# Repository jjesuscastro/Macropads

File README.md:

# Macropads

This repository contains the full source files for my custom-designed mechanical macropads, featuring integrated OLED displays and programmable keys via QMK with VIAL support.

## 🛠 Project Overview

This project includes two distinct designs tailored for different productivity needs:
* **Hesu12**: A compact 12-key layout with an OLED screen.
* **Hesu14**: An expanded 14-key layout with an OLED screen.

---

## 🎹 Hardware Specifications

Both boards are designed with a focus on ease of assembly and high-performance hardware:

* **Controller Support**: Designed for Pro Micro or RP2040 Zero
* **Display**: I2C OLED modules (128x32).
* **Switches**: MX-compatible mechanical switch footprints.
* **Connectivity**: USB-C (via controller).

| Feature | Hesu12 | Hesu14 |
| :--- | :--- | :--- |
| **Key Count** | 12 Keys | 14 Keys |
| **Display** | 1x OLED | 1x OLED |
| **EDA Tool** | KiCad 8.0+ | KiCad 8.0+ |

---

## 🚀 Firmware Installation
These macropads utilize **QMK (Quantum Mechanical Keyboard)** firmware.

1. Clone the official [QMK Firmware](https://github.com/qmk/qmk_firmware) repository.
2. Copy the contents of the `/Firmware` directory into your local `qmk_firmware/keyboards/` folder.
3. Compile and flash your board using the QMK CLI:

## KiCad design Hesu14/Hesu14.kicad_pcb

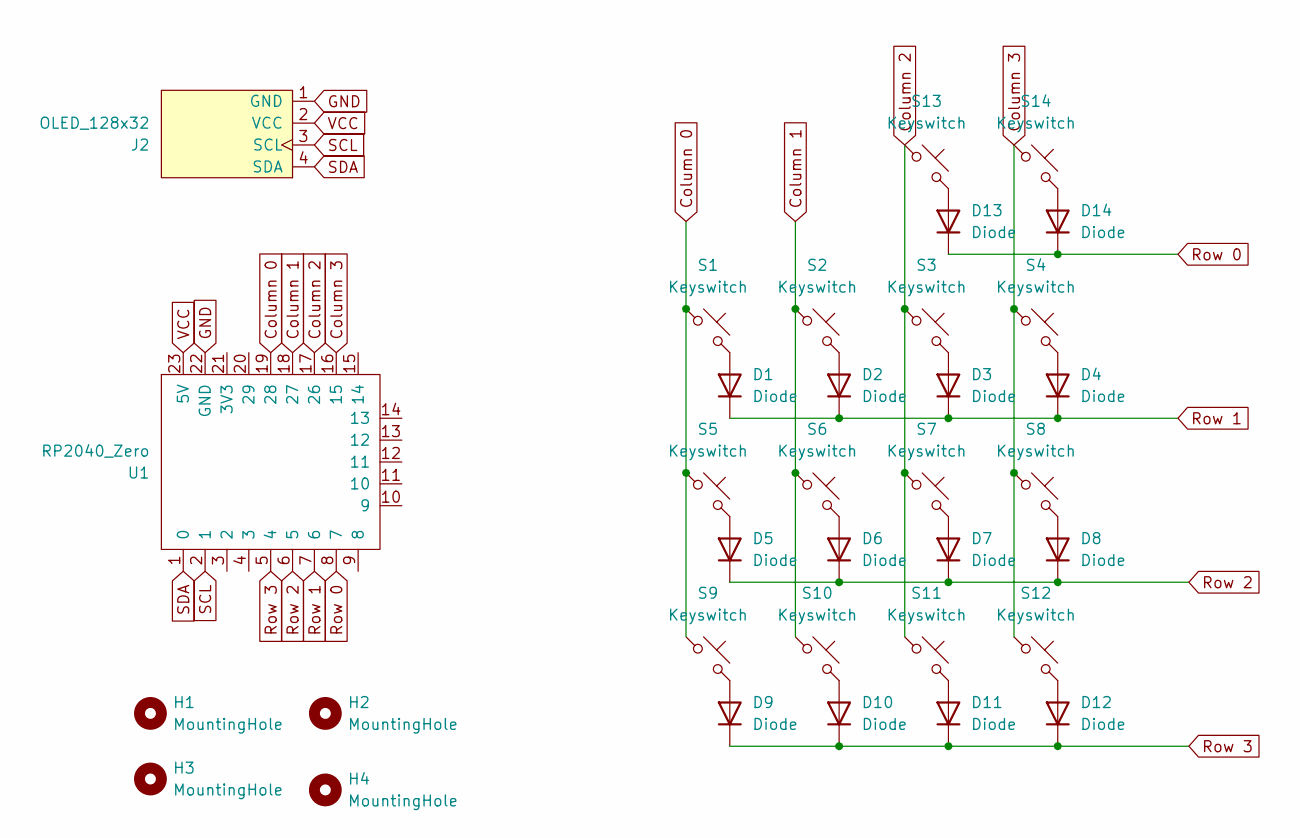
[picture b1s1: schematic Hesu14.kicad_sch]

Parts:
D1, D2, D3, D4, D5, D6, D7, D8, D9, D10, D11, D12, D13, D14: Diode; Diode_DO-35
H1, H2, H3, H4: MountingHole; MountingHole_2.5mm
J2: OLED_128x32
S1, S2, S3, S4, S5, S6, S7, S8, S9, S10, S11, S12, S13, S14: Keyswitch; Hotswap_MX_1.00u
U1: RP2040_Zero

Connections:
Column 0: S1.1, S5.1, S9.1, U1.19 (28)
Column 1: S2.1, S6.1, S10.1, U1.18 (27)
Column 2: S3.1, S7.1, S11.1, S13.1, U1.17 (26)
Column 3: S4.1, S8.1, S12.1, S14.1, U1.16 (15)
GND: J2.1 (GND), U1.22 (GND)
unnamed: D1.2 (A), S1.2
unnamed: D2.2 (A), S2.2
unnamed: D3.2 (A), S3.2
unnamed: D4.2 (A), S4.2
unnamed: D5.2 (A), S5.2
unnamed: D6.2 (A), S6.2
unnamed: D7.2 (A), S7.2
unnamed: D8.2 (A), S8.2
unnamed: D9.2 (A), S9.2
unnamed: D10.2 (A), S10.2
unnamed: D11.2 (A), S11.2
unnamed: D12.2 (A), S12.2
unnamed: D13.2 (A), S13.2
unnamed: D14.2 (A), S14.2
Row 0: D13.1 (K), D14.1 (K), U1.8 (7)
Row 1: D1.1 (K), D2.1 (K), D3.1 (K), D4.1 (K), U1.7 (6)
Row 2: D5.1 (K), D6.1 (K), D7.1 (K), D8.1 (K), U1.6 (5)
Row 3: D9.1 (K), D10.1 (K), D11.1 (K), D12.1 (K), U1.5 (4)
SCL: J2.3 (SCL), U1.2 (1)
SDA: J2.4 (SDA), U1.1 (0)
VCC: J2.2 (VCC), U1.23 (5V)

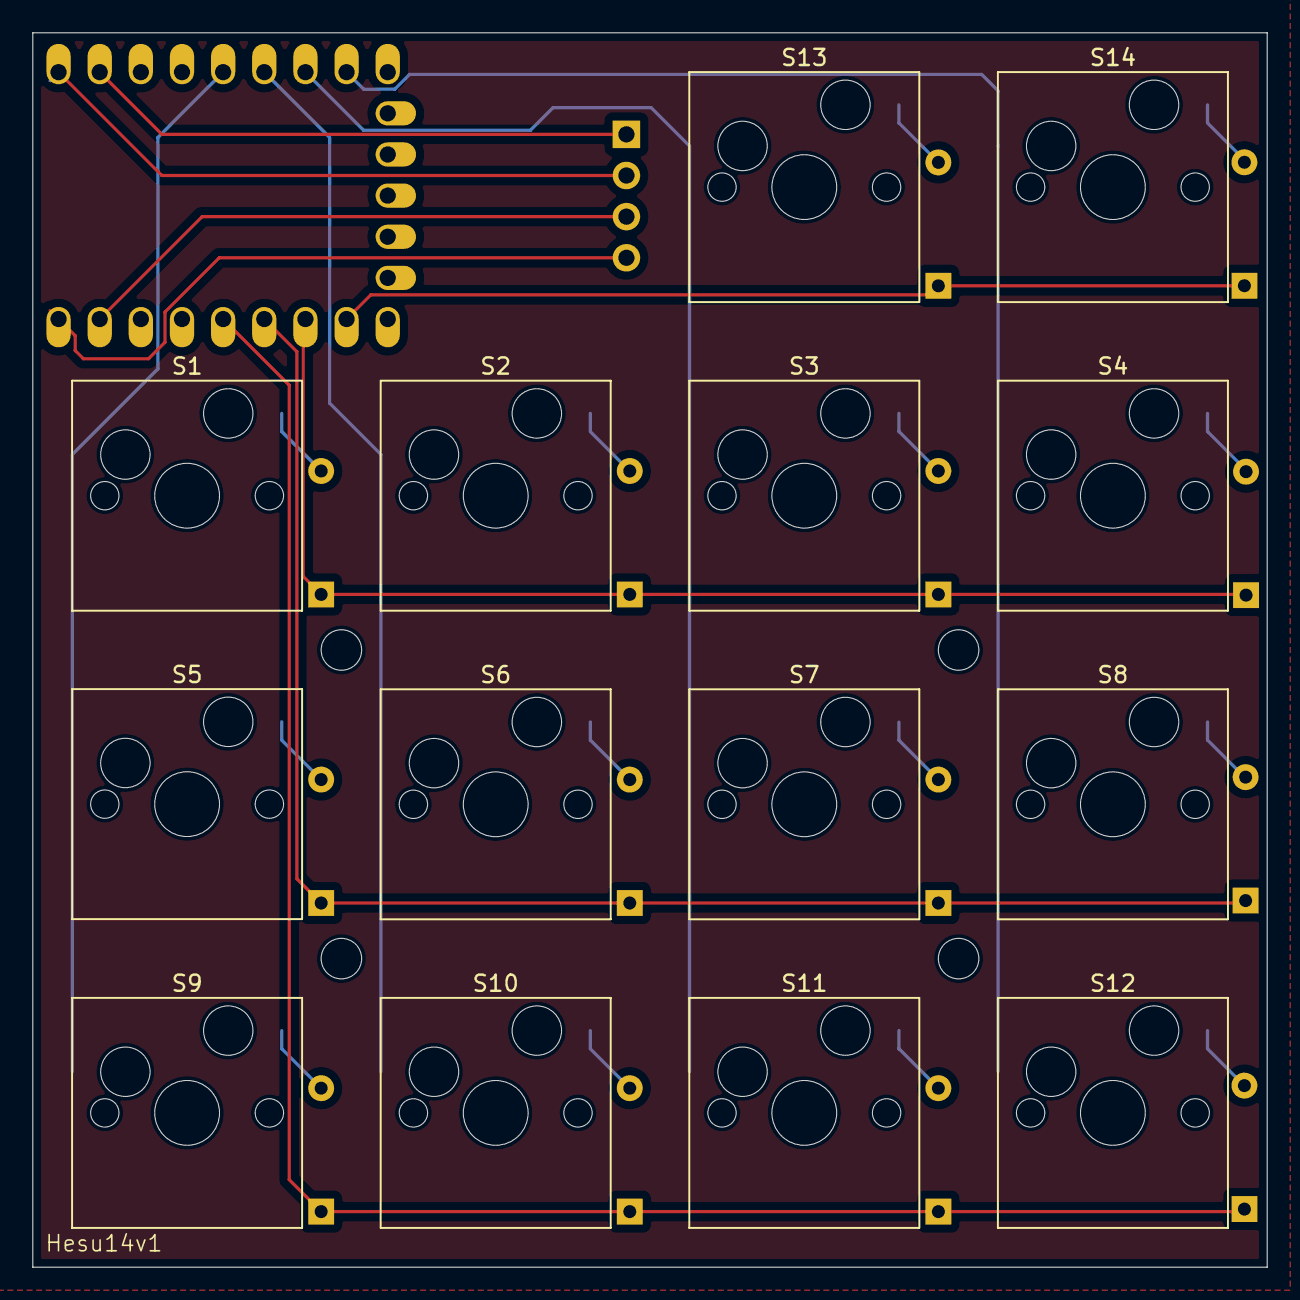
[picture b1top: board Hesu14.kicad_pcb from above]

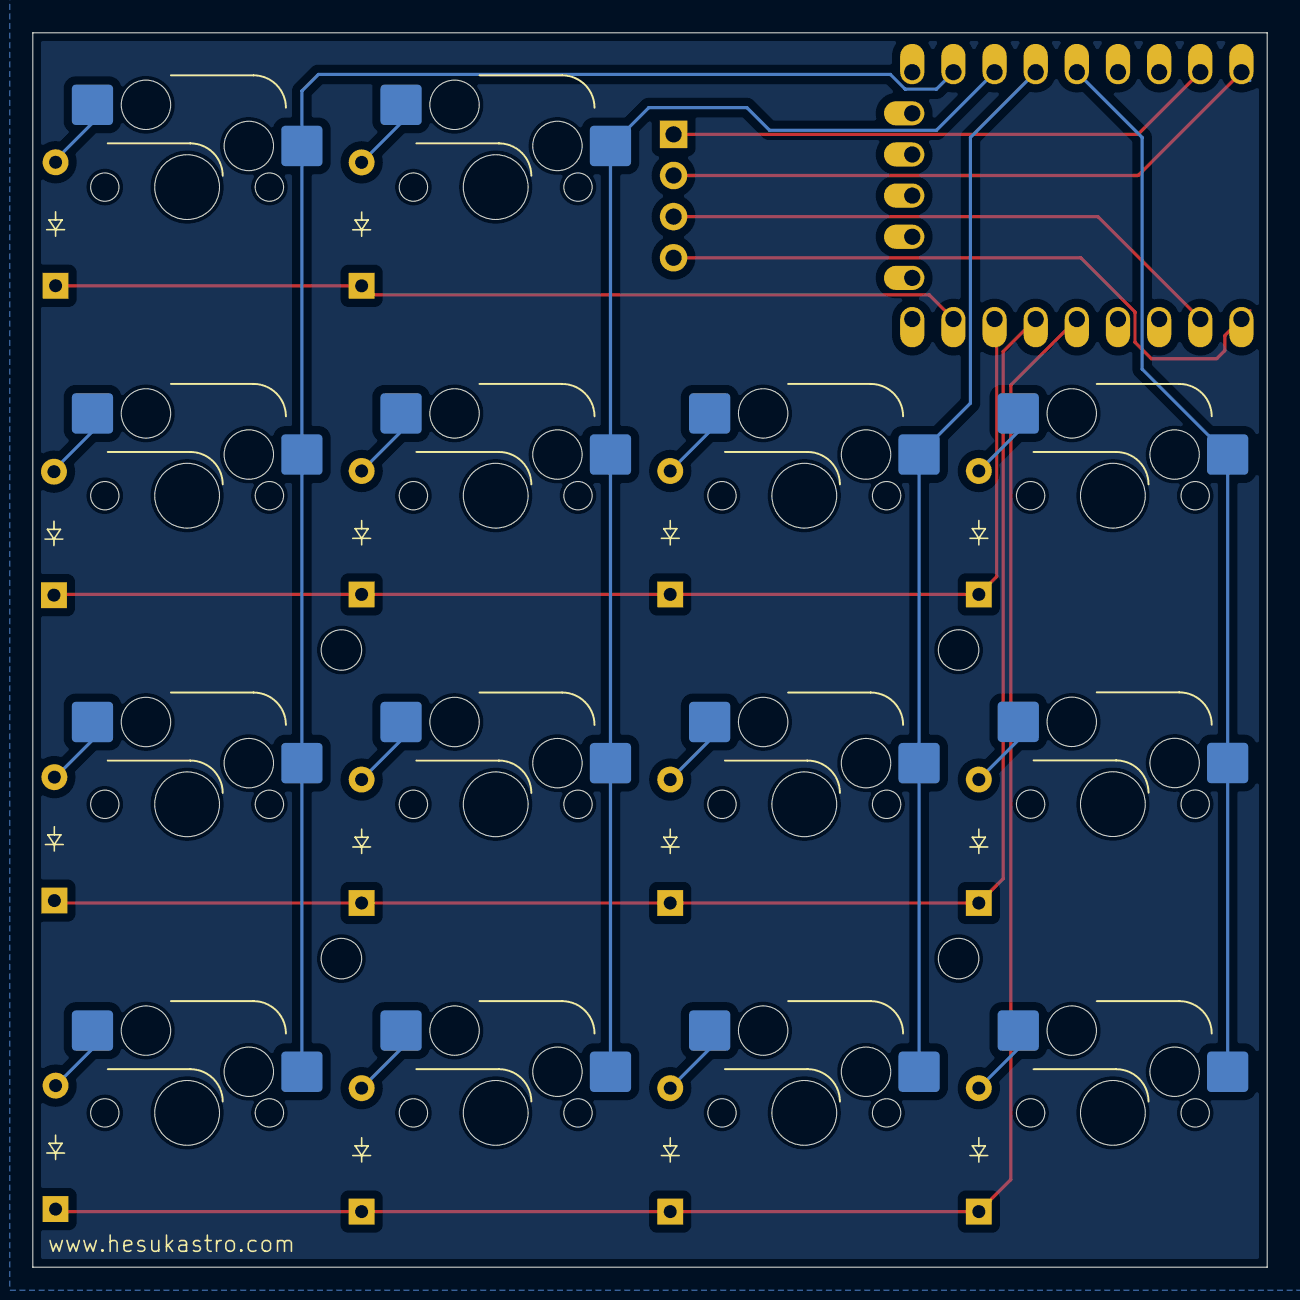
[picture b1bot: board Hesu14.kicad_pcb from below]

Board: 2 copper layers, 76.2 x 76.2 mm, 34 parts (15 on the bottom side), 26 nets.

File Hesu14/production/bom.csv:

Designator,Footprint,Quantity,Value,LCSC Part #
"D1, D10, D11, D12, D13, D14, D2, D3, D4, D5, D6, D7, D8, D9",Diode_DO-35,14,Diode,
J2,OLED_128x32,1,OLED_128x32,
"S1, S10, S11, S12, S13, S14, S2, S3, S4, S5, S6, S7, S8, S9",Hotswap_MX_1.00u,14,Keyswitch,
U1,RP2040_Zero,1,RP2040_Zero,

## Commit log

2025-08-07 Update PCB and Case
2025-08-09 Update Cases
2025-08-09 Add autohotkey scripts
2025-08-09 Vial Layout
2025-08-14 Update Case File
2025-08-14 Upload QMK and Vial Files
2025-08-15 OLED With Animation
2025-08-15 Change to QP
2025-08-15 Fix timeout
2025-08-17 Update VIAL Keymap
2025-08-17 Cleanup
2025-08-17 Add AHK Toggle
2025-08-18 Update VIAL
    - Center Status Text
    - Unregister F23 and F24 on AHK Toggle off
2025-08-18 Change Layer text to image
2026-01-07 Initialize README with project details
    Add project overview, hardware specifications, and firmware installation instructions for custom macropads.
